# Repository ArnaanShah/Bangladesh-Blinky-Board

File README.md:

# Bangladesh-Blinky-Board  
A Simple LED chaser in the shape of the flag of Bangladesh based on the Blinky Board tutorial from Stasis. The 10 red LEDs are arranged along the circle of the Bangladesh flag. There is a red 3d printed part to cover the white silkscreen and make the PCB resemble the flag more. This was a very fun simpler project to make and I liked that I could include something personal to me in it. It taught me how to use analog sensors. 

# Setup
The setup is very quick and can be done in 4 steps:

1. Order your PCB from [JLCPCB](https://jlcpcb.com)
2. Solder the components onto the board
3. Place the 3d printed circle on top of the LED ring
4. Power on your blinky board!

# PCB
The PCB was made in KiCad and it was very easy because most of the instructions were given by the tutorial. The schematic was a bit tricky because some of the individual part schematics looked different, but I was able to figure it out. Making the layout of the PCB made me learn how to use the array tool in KiCad. The routing was simple and I tried arranging the rest of the components in a way that would look nice. 

Schematic: 

PCB:

3d view:

# 3d Prints
There is one 3d printed part of the board and it's to make it look nicer and more accurate to the flag. It's a red circle that goes ontop of the LEDs that I made in Fusion360.

Images:

# BOM
There's only really 3 things you need for this build. You need the Blinky Board kit from Hackclub, the 3d printed circle, and a custom PCB.

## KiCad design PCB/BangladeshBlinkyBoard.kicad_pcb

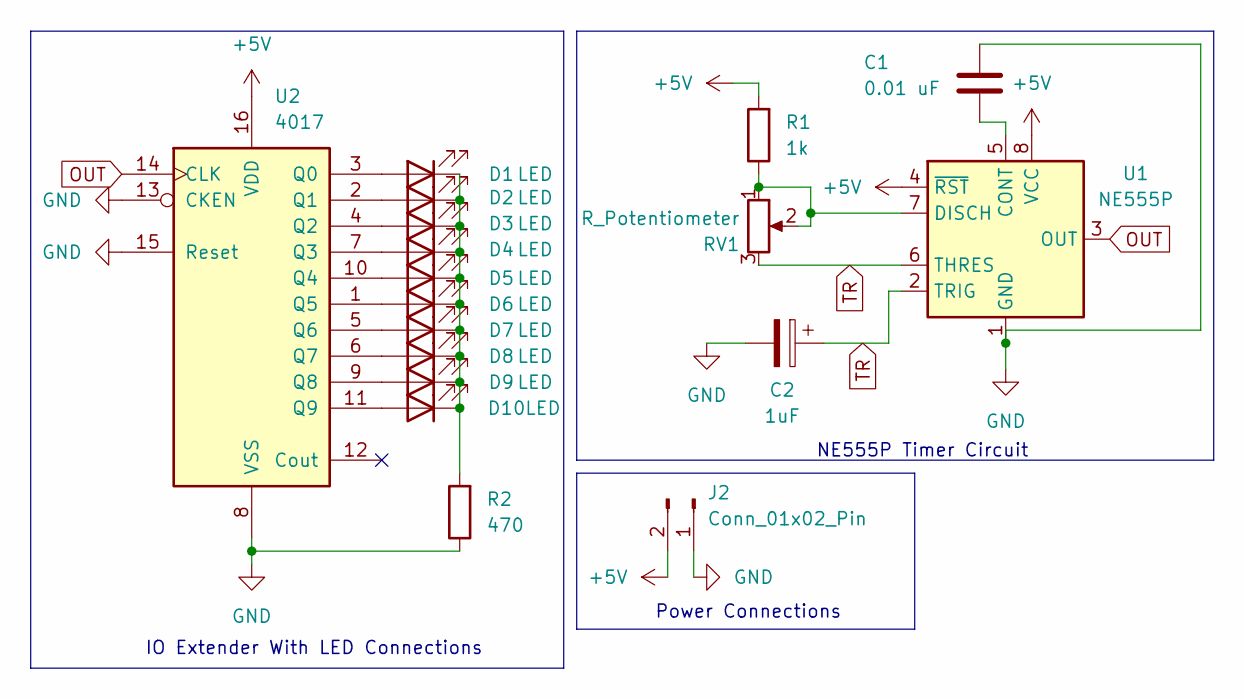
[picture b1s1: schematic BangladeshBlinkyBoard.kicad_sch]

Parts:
C1: 0.01 uF; C_Disc_D7.5mm_W2.5mm_P5.00mm
C2: 1uF; CP_Radial_D5.0mm_P2.00mm
D1, D2, D3, D4, D5, D6, D7, D8, D9, D10: LED; LED_D3.0mm
J2: Conn_01x02_Pin; PinHeader_1x02_P2.54mm_Vertical
R1: 1k; R_Axial_DIN0207_L6.3mm_D2.5mm_P7.62mm_Horizontal
R2: 470; R_Axial_DIN0207_L6.3mm_D2.5mm_P7.62mm_Horizontal
RV1: R_Potentiometer; Potentiometer_Vishay_T93YA_Vertical
U1: NE555P; DIP-8_W7.62mm
U2: 4017; N16

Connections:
+5V: J2.2, R1.2, U1.4 (~RST), U1.8 (VCC), U2.16 (VDD)
GND: C1.2, C2.2, J2.1, R2.1, U1.1 (GND), U2.8 (VSS), U2.13 (CKEN), U2.15 (Reset)
unnamed: D1.2 (A), U2.3 (Q0)
unnamed: D1.1 (K), D2.1 (K), D3.1 (K), D4.1 (K), D5.1 (K), D6.1 (K), D7.1 (K), D8.1 (K), D9.1 (K), D10.1 (K), R2.2
unnamed: D2.2 (A), U2.2 (Q1)
unnamed: D3.2 (A), U2.4 (Q2)
unnamed: D4.2 (A), U2.7 (Q3)
unnamed: D5.2 (A), U2.10 (Q4)
unnamed: D6.2 (A), U2.1 (Q5)
unnamed: D7.2 (A), U2.5 (Q6)
unnamed: D8.2 (A), U2.6 (Q7)
unnamed: D9.2 (A), U2.9 (Q8)
unnamed: D10.2 (A), U2.11 (Q9)
unnamed: C1.1, U1.5 (CONT)
unnamed: R1.1, RV1.1, RV1.2, U1.7 (DISCH)
OUT: U1.3 (OUT), U2.14 (CLK)
TR: C2.1, RV1.3, U1.2 (TRIG), U1.6 (THRES)

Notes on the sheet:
NE555P Timer Circuit
Power Connections
IO Extender With LED Connections

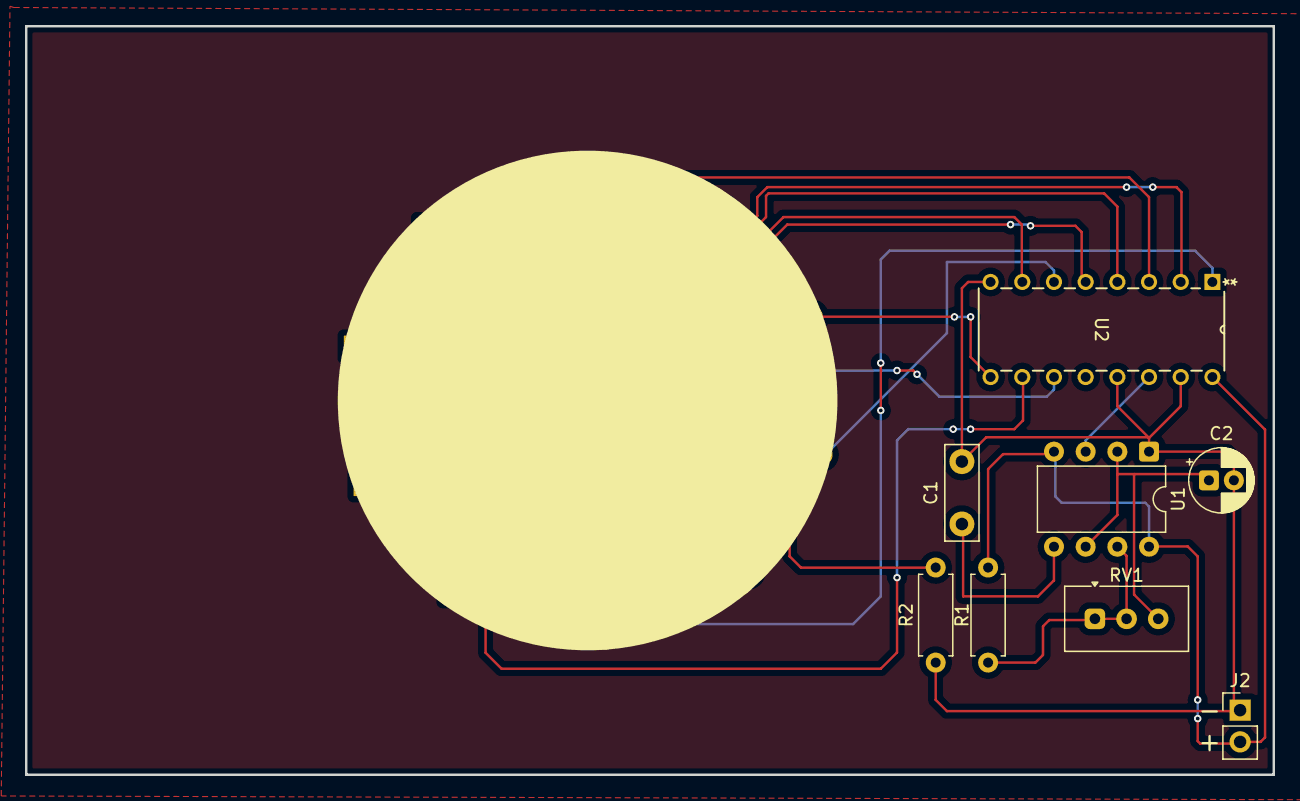
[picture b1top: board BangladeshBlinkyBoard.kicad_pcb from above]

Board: 2 copper layers, 100.0 x 60.0 mm, 18 parts (0 on the bottom side), 17 nets.

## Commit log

2026-05-03 Adding all required files PCB, CAD, BOM, Manufacturing
2026-05-03 Enhance README with project details and instructions
    Expanded the README with detailed project description, setup instructions, PCB design process, 3D print information, and BOM.
